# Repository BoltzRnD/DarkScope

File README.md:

(DarkScope is Still under development and might take until December 2019 for its first Functional Release.)

Darkscope is an ATSAME70Q21 Based, Open Source and Open Hardware, 4 Channel Portable DSO with Features Such as

1. 3.5" to 7" TFT
2. Internal Storage Options* (64 Mb - 256 Mb)
3. External Storage Support (MicroSD Cards and USB)
4. PC Based Expanded UI for Elaborated and Better Visualizations*.
5. Touch Screen Interface(This will be added at last.)
6. USB Type C Rev interface for Charging and Data Transfer.
7. Up to  5* MSPS (At 1 Active Channel) 
8. Up to  1* MSPS (At 4 Active Channels)

(* Chances are these will be improved by optimizing the firmware on every newer release.)

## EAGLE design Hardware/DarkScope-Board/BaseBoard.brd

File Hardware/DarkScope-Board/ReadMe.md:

# Scope

# HW Sections
1. A Baseboard that hosts All Processing (MCu and Supporting Circuitry, Expansion Ports for- Active Probe Shields, LCD, Switches) (Board 1)
2. Base Active Probe Board. i.e- Analog Channel (Board 2)
3. Battery Management Circuit(BMC) with 1500mAh or more Battery(Board 3)
4. High Speed Active Probe(Board 4)
5. Upto 4 Channel Support (Exposing/Utilizing PA0, PA4, PA5, PA6) (On BaseBoard 1)
6. (Optional) I2C Based Switch Board.(On BaseBoard 1)

Note-
1. LCD "LED-A" connected to 5V for now, can be changed to vcc

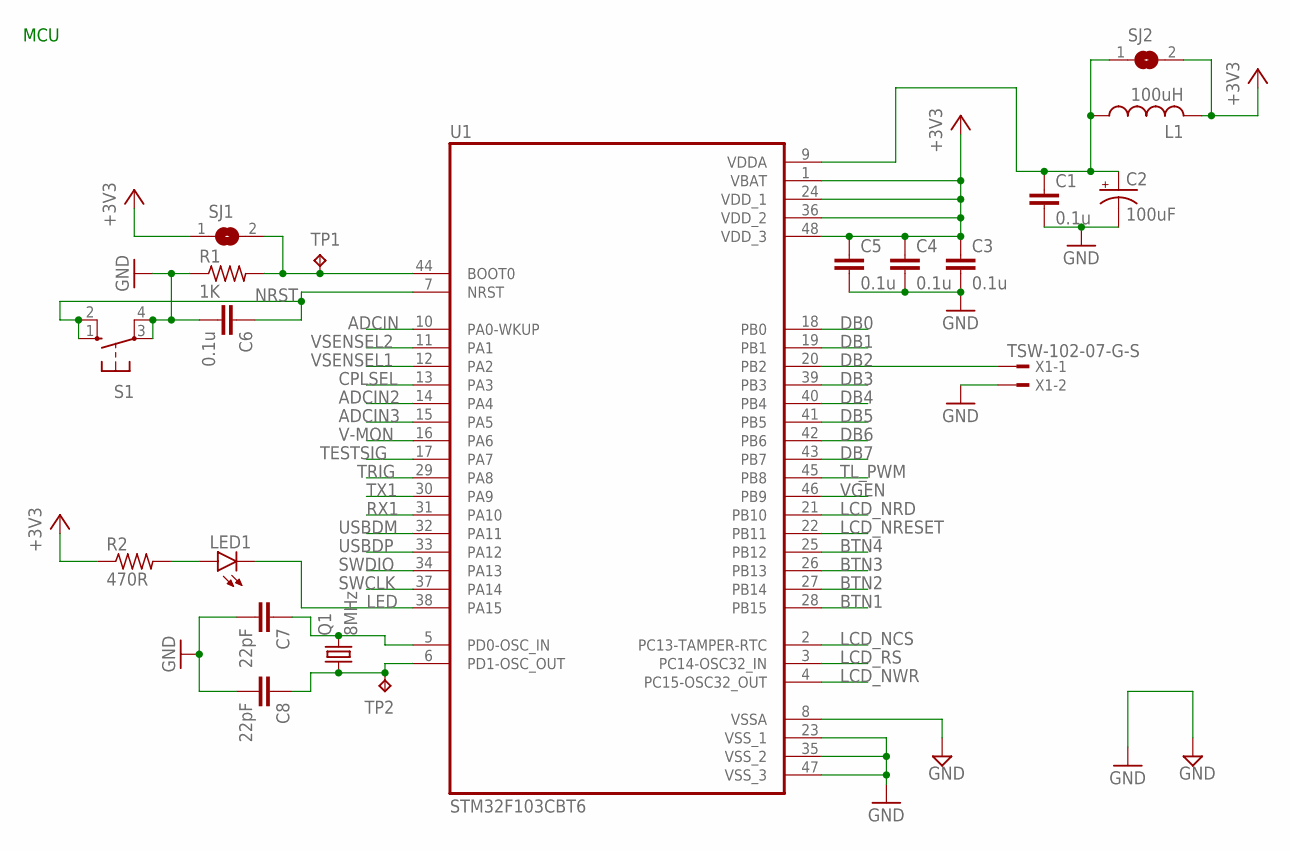
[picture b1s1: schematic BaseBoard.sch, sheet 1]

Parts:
C1, C3, C4, C5, C6: 0.1u; C1206
C2: 100uF; CT6032
C7, C8: 22pF; C1206
L1: 100uH; 0204/5
LED1: LEDCHIPLED_1206; CHIPLED_1206
Q1: 8MHz; HC49/S
R1: 1K; R0805
R2: 470R; R0805
S1: 10-XX; B3F-10XX
SJ1, SJ2: SJW
TP1, TP2: TPB1,27; B1,27
U1: STM32F103CBT6; QFP50P900X900X160-48N
X1: TSW-102-07-G-S; TSW-102-XX-G-S

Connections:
+3V3: C3.1, C4.1, C5.1, L1.2, R2.1, SJ1.1, SJ2.2, U1.1 (VBAT), U1.24 (VDD_1), U1.36 (VDD_2), U1.48 (VDD_3); also elsewhere on the board
ADCIN: U1.10 (PA0-WKUP); also elsewhere on the board
ADCIN2: U1.14 (PA4); also elsewhere on the board
ADCIN3: U1.15 (PA5); also elsewhere on the board
BTN1: U1.28 (PB15); also elsewhere on the board
BTN2: U1.27 (PB14); also elsewhere on the board
BTN3: U1.26 (PB13); also elsewhere on the board
BTN4: U1.25 (PB12); also elsewhere on the board
CPLSEL: U1.13 (PA3); also elsewhere on the board
DB0: U1.18 (PB0); also elsewhere on the board
DB1: U1.19 (PB1); also elsewhere on the board
DB2: U1.20 (PB2), X1.1; also elsewhere on the board
DB3: U1.39 (PB3); also elsewhere on the board
DB4: U1.40 (PB4); also elsewhere on the board
DB5: U1.41 (PB5); also elsewhere on the board
DB6: U1.42 (PB6); also elsewhere on the board
DB7: U1.43 (PB7); also elsewhere on the board
GND: C1.2, C2.-, C3.2, C4.2, C5.2, C6.2, C7.2, C8.2, R1.1, S1.3, S1.4 (P1), U1.8 (VSSA), U1.23 (VSS_1), U1.35 (VSS_2), U1.47 (VSS_3), X1.2; also elsewhere on the board
LCD_NCS: U1.2 (PC13-TAMPER-RTC); also elsewhere on the board
LCD_NRD: U1.21 (PB10); also elsewhere on the board
LCD_NRESET: U1.22 (PB11); also elsewhere on the board
LCD_NWR: U1.4 (PC15-OSC32_OUT); also elsewhere on the board
LCD_RS: U1.3 (PC14-OSC32_IN); also elsewhere on the board
LED: LED1.C, U1.38 (PA15); also elsewhere on the board
unnamed: C1.1, C2.+, L1.1, SJ2.1, U1.9 (VDDA)
unnamed: LED1.A, R2.2
unnamed: R1.2, SJ1.2, TP1.TP, U1.44 (BOOT0)
unnamed: C7.1, Q1.2, U1.5 (PD0-OSC_IN)
unnamed: C8.1, Q1.1, TP2.TP, U1.6 (PD1-OSC_OUT)
NRST: C6.1, S1.1 (S), S1.2 (S1), U1.7 (NRST); also elsewhere on the board
RX1: U1.31 (PA10); also elsewhere on the board
SWCLK: U1.37 (PA14); also elsewhere on the board
SWDIO: U1.34 (PA13); also elsewhere on the board
TESTSIG: U1.17 (PA7); also elsewhere on the board
TL_PWM: U1.45 (PB8); also elsewhere on the board
TRIG: U1.29 (PA8); also elsewhere on the board
TX1: U1.30 (PA9); also elsewhere on the board
USBDM: U1.32 (PA11); also elsewhere on the board
USBDP: U1.33 (PA12); also elsewhere on the board
V-MON: U1.16 (PA6); also elsewhere on the board
VGEN: U1.46 (PB9); also elsewhere on the board
VSENSEL1: U1.12 (PA2); also elsewhere on the board
VSENSEL2: U1.11 (PA1); also elsewhere on the board

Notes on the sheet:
MCU

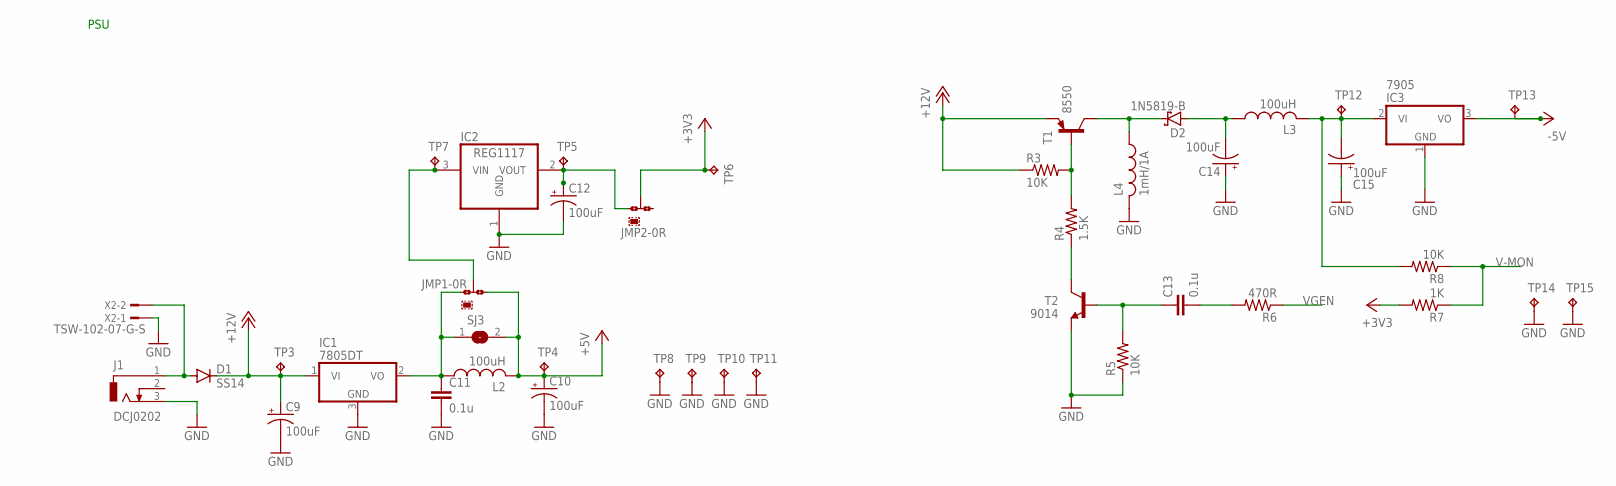
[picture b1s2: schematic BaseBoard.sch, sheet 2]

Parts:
C9, C10, C12, C14, C15: 100uF; CT6032
C11, C13: 0.1u; C1206
D1: SS14; SMB
D2: 1N5819-B; DO41-7.6
IC1: 7805DT; TO252
IC2: REG1117; SOT223
IC3: 7905; TO92
J1: DCJ0202
JMP1, JMP2: 0R-JUMPA; A0R-JMP
L2, L3: 100uH; 0204/5
L4: 1mH/1A; 6000-XXXX-RC
R3, R5, R8: 10K; R0805
R4: 1.5K; R0805
R6: 470R; R0805
R7: 1K; R0805
SJ3: SJW
T1: 8550; TO92
T2: 9014; TO92
TP3, TP4, TP5, TP6, TP7, TP8, TP9, TP10, TP11, TP12, TP13, TP14, TP15: TPB1,27; B1,27
X2: TSW-102-07-G-S; TSW-102-XX-G-S

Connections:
+3V3: JMP2.2, R7.2, TP6.TP; also elsewhere on the board
+5V: C10.+, JMP1.3, L2.2, SJ3.2, TP4.TP; also elsewhere on the board
+12V: C9.+, D1.C, IC1.1 (VI), R3.1, T1.1 (E), TP3.TP; also elsewhere on the board
-5V: IC3.3 (VO), TP13.TP; also elsewhere on the board
GND: C9.-, C10.-, C11.2, C12.-, C14.+, C15.+, IC1.3 (GND), IC2.1 (GND), IC3.1 (GND), J1.3, L4.2, R5.1, T2.1 (E), TP8.TP, TP9.TP, TP10.TP, TP11.TP, TP14.TP, TP15.TP, X2.1; also elsewhere on the board
unnamed: C11.1, IC1.2 (VO), JMP1.1, L2.1, SJ3.1
unnamed: R3.2, R4.2, T1.2 (B)
unnamed: C12.+, IC2.2 (VOUT), JMP2.1, TP5.TP
unnamed: R4.1, T2.3 (C)
unnamed: C13.1, R5.2, T2.2 (B)
unnamed: IC2.3 (VIN), JMP1.2, TP7.TP
unnamed: C13.2, R6.2
unnamed: D2.C, L4.1, T1.3 (C)
unnamed: C14.-, D2.A, L3.1
unnamed: C15.-, IC3.2 (VI), L3.2, R8.2, TP12.TP
unnamed: D1.A, J1.1, X2.2
V-MON: R7.1, R8.1; also elsewhere on the board
VGEN: R6.1; also elsewhere on the board

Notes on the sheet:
PSU

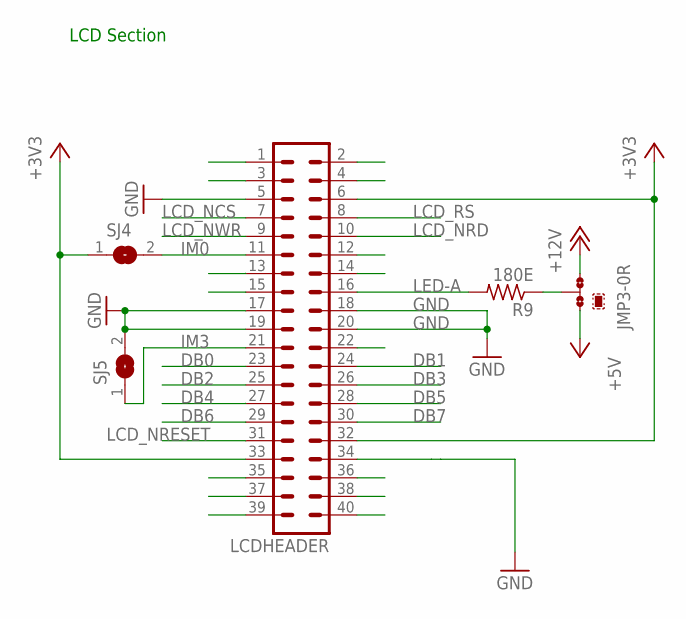
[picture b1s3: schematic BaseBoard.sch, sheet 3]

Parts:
JMP3: 0R-JUMPA; A0R-JMP
LCDHEADER: MA20-2
R9: 180E; R0805
SJ4, SJ5: SJ

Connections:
+3V3: LCDHEADER.6, LCDHEADER.32, LCDHEADER.33, SJ4.1; also elsewhere on the board
+5V: JMP3.1; also elsewhere on the board
+12V: JMP3.3; also elsewhere on the board
DB0: LCDHEADER.23; also elsewhere on the board
DB1: LCDHEADER.24; also elsewhere on the board
DB2: LCDHEADER.25; also elsewhere on the board
DB3: LCDHEADER.26; also elsewhere on the board
DB4: LCDHEADER.27; also elsewhere on the board
DB5: LCDHEADER.28; also elsewhere on the board
DB6: LCDHEADER.29; also elsewhere on the board
DB7: LCDHEADER.30; also elsewhere on the board
GND: LCDHEADER.5, LCDHEADER.17, LCDHEADER.18, LCDHEADER.19, LCDHEADER.20, LCDHEADER.34, SJ5.2; also elsewhere on the board
IM0: LCDHEADER.11, SJ4.2
IM3: LCDHEADER.21, SJ5.1
LCD_NCS: LCDHEADER.7; also elsewhere on the board
LCD_NRD: LCDHEADER.10; also elsewhere on the board
LCD_NRESET: LCDHEADER.31; also elsewhere on the board
LCD_NWR: LCDHEADER.9; also elsewhere on the board
LCD_RS: LCDHEADER.8; also elsewhere on the board
LED-A: LCDHEADER.16, R9.2
LED-K1: LCDHEADER.15
unnamed: JMP3.2, R9.1

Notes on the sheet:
LCD Section

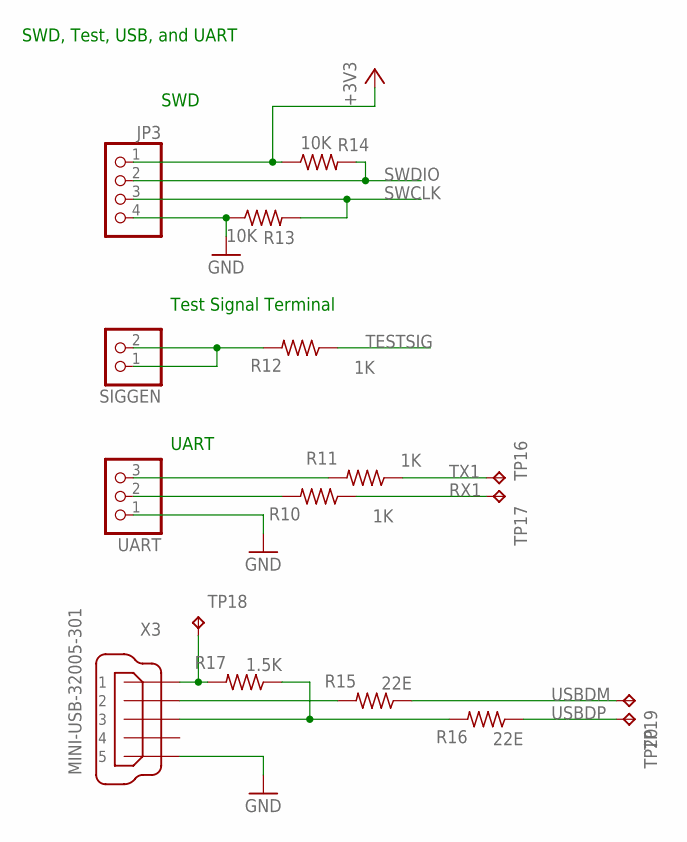
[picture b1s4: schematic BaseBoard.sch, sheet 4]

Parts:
JP3: PINHD-1X4; 1X04
R10, R11, R12: 1K; R0805
R13, R14: 10K; R0805
R15, R16: 22E; R0805
R17: 1.5K; R0805
SIGGEN: PINHD-1X2; 1X02
TP16, TP17, TP18, TP19, TP20: TPB1,27; B1,27
UART: PINHD-1X3; 1X03
X3: MINI-USB-32005-301; 32005-301

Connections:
+3V3: JP3.1, R14.1; also elsewhere on the board
GND: JP3.4, R13.1, UART.1, X3.5; also elsewhere on the board
unnamed: R10.2, UART.2
unnamed: R11.2, UART.3
unnamed: R12.2, SIGGEN.1, SIGGEN.2
unnamed: R17.2, TP18.TP, X3.1
unnamed: R16.2, R17.1, X3.3
unnamed: R15.2, X3.2
RX1: R10.1, TP17.TP; also elsewhere on the board
SWCLK: JP3.3, R13.2; also elsewhere on the board
SWDIO: JP3.2, R14.2; also elsewhere on the board
TESTSIG: R12.1; also elsewhere on the board
TX1: R11.1, TP16.TP; also elsewhere on the board
USBDM: R15.1, TP19.TP; also elsewhere on the board
USBDP: R16.1, TP20.TP; also elsewhere on the board

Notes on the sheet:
SWD, Test, USB, and UART
UART
Test Signal Terminal
SWD

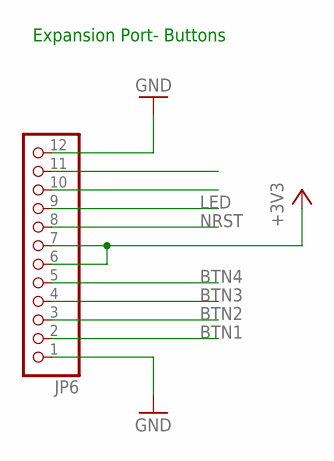
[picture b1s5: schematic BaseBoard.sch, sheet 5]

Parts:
JP6: PINHD-1X12; 1X12

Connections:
+3V3: JP6.6, JP6.7; also elsewhere on the board
BTN1: JP6.2; also elsewhere on the board
BTN2: JP6.3; also elsewhere on the board
BTN3: JP6.4; also elsewhere on the board
BTN4: JP6.5; also elsewhere on the board
GND: JP6.1, JP6.12; also elsewhere on the board
LED: JP6.9; also elsewhere on the board
NRST: JP6.8; also elsewhere on the board

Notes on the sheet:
Expansion Port- Buttons

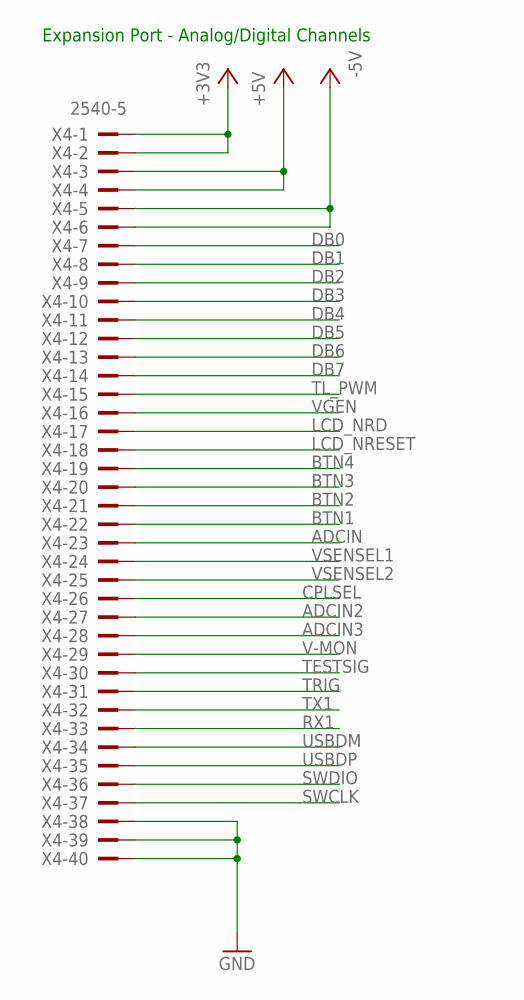
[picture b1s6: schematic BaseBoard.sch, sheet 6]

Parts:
X4: 2540-5; PAK100/2500-5-40

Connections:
+3V3: X4.1, X4.2; also elsewhere on the board
+5V: X4.3, X4.4; also elsewhere on the board
-5V: X4.5, X4.6; also elsewhere on the board
ADCIN: X4.23; also elsewhere on the board
ADCIN2: X4.27; also elsewhere on the board
ADCIN3: X4.28; also elsewhere on the board
BTN1: X4.22; also elsewhere on the board
BTN2: X4.21; also elsewhere on the board
BTN3: X4.20; also elsewhere on the board
BTN4: X4.19; also elsewhere on the board
CPLSEL: X4.26; also elsewhere on the board
DB0: X4.7; also elsewhere on the board
DB1: X4.8; also elsewhere on the board
DB2: X4.9; also elsewhere on the board
DB3: X4.10; also elsewhere on the board
DB4: X4.11; also elsewhere on the board
DB5: X4.12; also elsewhere on the board
DB6: X4.13; also elsewhere on the board
DB7: X4.14; also elsewhere on the board
GND: X4.38, X4.39, X4.40; also elsewhere on the board
LCD_NRD: X4.17; also elsewhere on the board
LCD_NRESET: X4.18; also elsewhere on the board
RX1: X4.33; also elsewhere on the board
SWCLK: X4.37; also elsewhere on the board
SWDIO: X4.36; also elsewhere on the board
TESTSIG: X4.30; also elsewhere on the board
TL_PWM: X4.15; also elsewhere on the board
TRIG: X4.31; also elsewhere on the board
TX1: X4.32; also elsewhere on the board
USBDM: X4.34; also elsewhere on the board
USBDP: X4.35; also elsewhere on the board
V-MON: X4.29; also elsewhere on the board
VGEN: X4.16; also elsewhere on the board
VSENSEL1: X4.24; also elsewhere on the board
VSENSEL2: X4.25; also elsewhere on the board

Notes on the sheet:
Expansion Port - Analog/Digital Channels

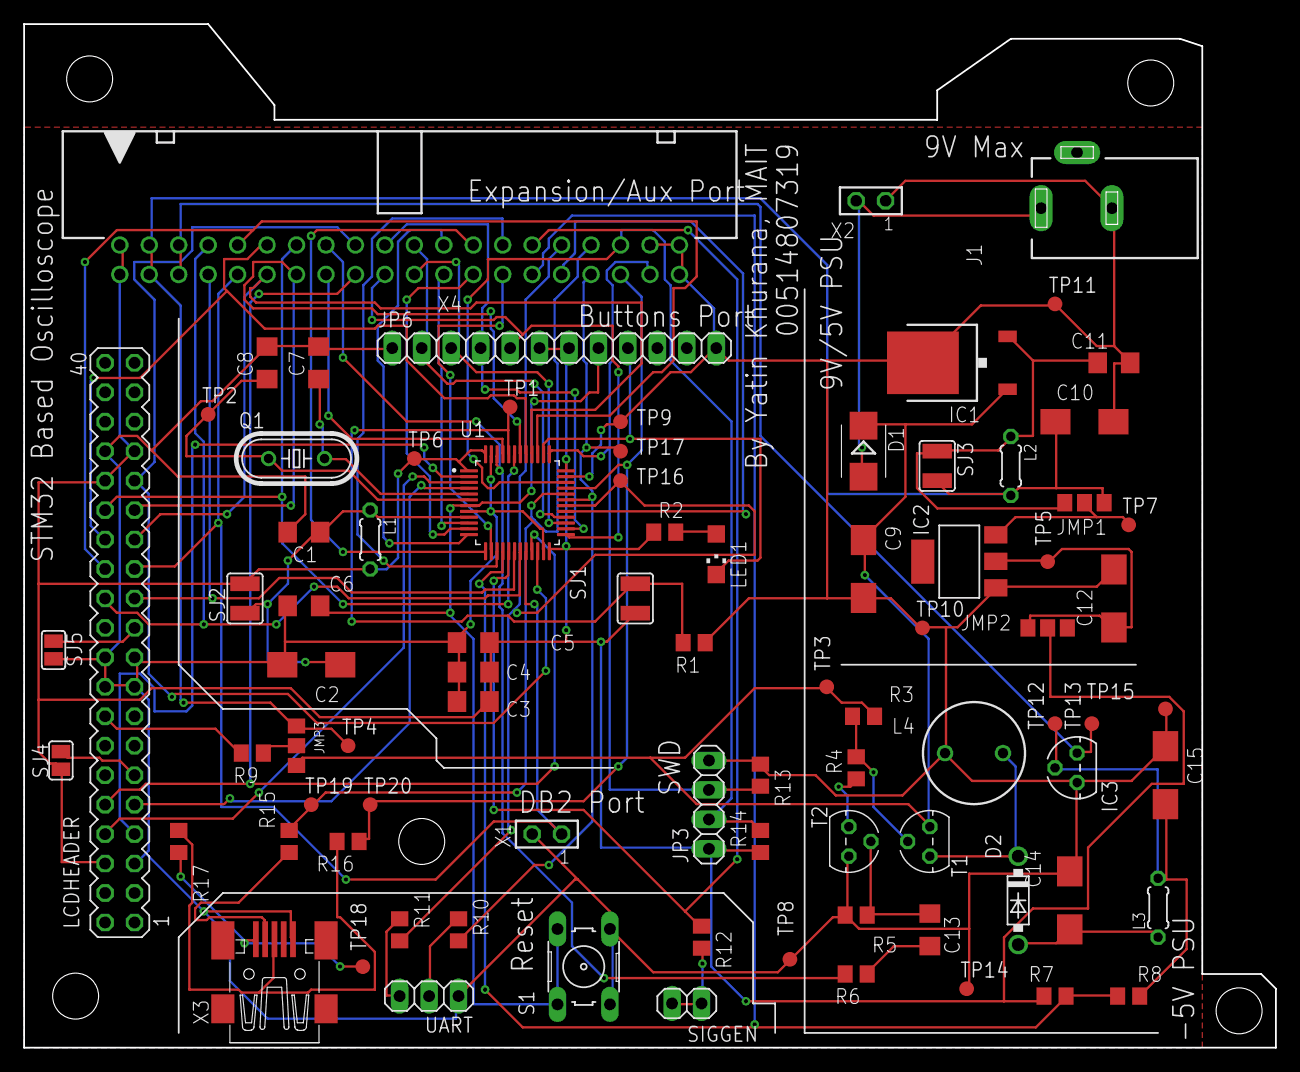
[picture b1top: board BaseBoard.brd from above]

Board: 2 copper layers, 108.0 x 88.3 mm, 90 parts (0 on the bottom side), 67 nets.

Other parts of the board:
U$1, U$2, U$3, U$4, U$5: DRILL_0.1560

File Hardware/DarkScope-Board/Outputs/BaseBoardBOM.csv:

Part,Value,Device,Package,Description,AVAILABILITY,DESCRIPTION,MF,MP,MPN,OC_FARNELL,OC_NEWARK,PACKAGE,POPULARITY,PRICE,PURCHASE-URL,SPICEPREFIX,TP_SIGNAL_NAME
C1,0.1u,C-EUC1206,C1206,"CAPACITOR, European symbol",,,,,,,,,54,,,C,
C2,100uF,CPOL-USCT6032,CT6032,"POLARIZED CAPACITOR, American symbol",,,,,,,,,0,,,C,
C3,0.1u,C-EUC1206,C1206,"CAPACITOR, European symbol",,,,,,,,,54,,,C,
C4,0.1u,C-EUC1206,C1206,"CAPACITOR, European symbol",,,,,,,,,54,,,C,
C5,0.1u,C-EUC1206,C1206,"CAPACITOR, European symbol",,,,,,,,,54,,,C,
C6,0.1u,C-EUC1206,C1206,"CAPACITOR, European symbol",,,,,,,,,54,,,C,
C7,22pF,C-EUC1206,C1206,"CAPACITOR, European symbol",,,,,,,,,54,,,C,
C8,22pF,C-EUC1206,C1206,"CAPACITOR, European symbol",,,,,,,,,54,,,C,
C9,100uF,CPOL-USCT6032,CT6032,"POLARIZED CAPACITOR, American symbol",,,,,,,,,0,,,C,
C10,100uF,CPOL-USCT6032,CT6032,"POLARIZED CAPACITOR, American symbol",,,,,,,,,0,,,C,
C11,0.1u,C-EUC1206,C1206,"CAPACITOR, European symbol",,,,,,,,,54,,,C,
C12,100uF,CPOL-USCT6032,CT6032,"POLARIZED CAPACITOR, American symbol",,,,,,,,,0,,,C,
C13,0.1u,C-EUC1206,C1206,"CAPACITOR, European symbol",,,,,,,,,54,,,C,
C14,100uF,CPOL-USCT6032,CT6032,"POLARIZED CAPACITOR, American symbol",,,,,,,,,0,,,C,
C15,100uF,CPOL-USCT6032,CT6032,"POLARIZED CAPACITOR, American symbol",,,,,,,,,0,,,C,
D1,SS14,ES2D,SMB,DIODE,,,,,,,,,3,,,,
D2,1N5819-B,1N5819-B,DO41-7.6,1.0A SCHOTTKY BARRIER RECTIFIER,,,,,,,,,11,,,,
IC1,7805DT,7805DT,TO252,Positive VOLTAGE REGULATOR,,,,,,,,,0,,,,
IC2,REG1117,REG1117,SOT223,800mA and 1A Low Dropout (LDO) Positive Regulator,,,,,REG1117,1097566,14P6981,,49,,,,
IC3,7905,79L05Z,TO92,Negative VOLTAGE REGULATOR,,,,,,,,,0,,,,
J1,DCJ0202,DCJ0202,DCJ0202,DC POWER JACK,,,,,,unknown,unknown,,17,,,,
JMP1,0R-JUMPC,0R-JUMPC,C0R-JMP,SMD 0R 0805 Jumper,,,,,,,,,0,,,,
JMP2,0R-JUMPC,0R-JUMPC,C0R-JMP,SMD 0R 0805 Jumper,,,,,,,,,0,,,,
JMP3,0R-JUMPC,0R-JUMPC,C0R-JMP,SMD 0R 0805 Jumper,,,,,,,,,0,,,,
JP3,,PINHD-1X4,1X04,PIN HEADER,,,,,,,,,91,,,,
JP6,,PINHD-1X12,1X12,PIN HEADER,,,,,,,,,28,,,,
L1,100uH,L-US0204/5,0204/5,"INDUCTOR, American symbol",,,,,,,,,0,,,L,
L2,100uH,L-US0204/5,0204/5,"INDUCTOR, American symbol",,,,,,,,,0,,,L,
L3,100uH,L-US0204/5,0204/5,"INDUCTOR, American symbol",,,,,,,,,0,,,L,
L4,1mH/1A,L-US6000-XXX-RC,6000-XXXX-RC,"INDUCTOR, American symbol",,,,,,,,,5,,,L,
LCDHEADER,,MA20-2,MA20-2,PIN HEADER,,,,,,unknown,unknown,,1,,,,
LED1,,LEDCHIPLED_1206,CHIPLED_1206,LED,,,,,,,,,28,,,,
Q1,8MHz,CRYSTALHC49S,HC49/S,CRYSTAL,,,,,,1667008,unknown,,49,,,,
R1,1K,R-US_R0805,R0805,"RESISTOR, American symbol",,,,,,,,,85,,,R,
R2,470R,R-US_R0805,R0805,"RESISTOR, American symbol",,,,,,,,,85,,,R,
R3,10K,R-US_R0805,R0805,"RESISTOR, American symbol",,,,,,,,,85,,,R,
R4,1.5K,R-US_R0805,R0805,"RESISTOR, American symbol",,,,,,,,,85,,,R,
R5,10K,R-US_R0805,R0805,"RESISTOR, American symbol",,,,,,,,,85,,,R,
R6,470R,R-US_R0805,R0805,"RESISTOR, American symbol",,,,,,,,,85,,,R,
R7,1K,R-US_R0805,R0805,"RESISTOR, American symbol",,,,,,,,,85,,,R,
R8,10K,R-US_R0805,R0805,"RESISTOR, American symbol",,,,,,,,,85,,,R,
R9,180E,R-US_R0805,R0805,"RESISTOR, American symbol",,,,,,,,,85,,,R,
R10,1K,R-US_R0805,R0805,"RESISTOR, American symbol",,,,,,,,,85,,,R,
R11,1K,R-US_R0805,R0805,"RESISTOR, American symbol",,,,,,,,,85,,,R,
R12,1K,R-US_R0805,R0805,"RESISTOR, American symbol",,,,,,,,,85,,,R,
R13,10K,R-US_R0805,R0805,"RESISTOR, American symbol",,,,,,,,,85,,,R,
R14,10K,R-US_R0805,R0805,"RESISTOR, American symbol",,,,,,,,,85,,,R,
R15,22E,R-US_R0805,R0805,"RESISTOR, American symbol",,,,,,,,,85,,,R,
R16,22E,R-US_R0805,R0805,"RESISTOR, American symbol",,,,,,,,,85,,,R,
R17,1.5K,R-US_R0805,R0805,"RESISTOR, American symbol",,,,,,,,,85,,,R,
S1,,10-XX,B3F-10XX,OMRON SWITCH,,,,,B3F-1000,176432,36M3542,,72,,,,
SIGGEN,,PINHD-1X2,1X02,PIN HEADER,,,,,,,,,98,,,,
SJ1,,SJW,SJW,SMD solder JUMPER,,,,,,,,,3,,,,
SJ2,,SJW,SJW,SMD solder JUMPER,,,,,,,,,3,,,,
SJ3,,SJW,SJW,SMD solder JUMPER,,,,,,,,,3,,,,
SJ4,,SJ,SJ,SMD solder JUMPER,,,,,,,,,33,,,,
SJ5,,SJ,SJ,SMD solder JUMPER,,,,,,,,,33,,,,
T1,8550,#NAME?,TO92,PNP Transistror,,,,,,,,,0,,,,
T2,9014,#NAME?,TO92,NPN Transistror,,,,,,,,,0,,,,
TP1,"TPB1,27","TPB1,27","B1,27",Test pad,,,,,,,,,19,,,,
TP2,"TPB1,27","TPB1,27","B1,27",Test pad,,,,,,,,,19,,,,
TP3,"TPB1,27","TPB1,27","B1,27",Test pad,,,,,,,,,19,,,,
TP4,"TPB1,27","TPB1,27","B1,27",Test pad,,,,,,,,,19,,,,
TP5,"TPB1,27","TPB1,27","B1,27",Test pad,,,,,,,,,19,,,,
TP6,"TPB1,27","TPB1,27","B1,27",Test pad,,,,,,,,,19,,,,
TP7,"TPB1,27","TPB1,27","B1,27",Test pad,,,,,,,,,19,,,,
TP8,"TPB1,27","TPB1,27","B1,27",Test pad,,,,,,,,,19,,,,
TP9,"TPB1,27","TPB1,27","B1,27",Test pad,,,,,,,,,19,,,,
TP10,"TPB1,27","TPB1,27","B1,27",Test pad,,,,,,,,,19,,,,
TP11,"TPB1,27","TPB1,27","B1,27",Test pad,,,,,,,,,19,,,,
TP12,"TPB1,27","TPB1,27","B1,27",Test pad,,,,,,,,,19,,,,
TP13,"TPB1,27","TPB1,27","B1,27",Test pad,,,,,,,,,19,,,,
TP14,"TPB1,27","TPB1,27","B1,27",Test pad,,,,,,,,,19,,,,
TP15,"TPB1,27","TPB1,27","B1,27",Test pad,,,,,,,,,19,,,,
TP16,"TPB1,27","TPB1,27","B1,27",Test pad,,,,,,,,,19,,,,
TP17,"TPB1,27","TPB1,27","B1,27",Test pad,,,,,,,,,19,,,,
TP18,"TPB1,27","TPB1,27","B1,27",Test pad,,,,,,,,,19,,,,
TP19,"TPB1,27","TPB1,27","B1,27",Test pad,,,,,,,,,19,,,,
TP20,"TPB1,27","TPB1,27","B1,27",Test pad,,,,,,,,,19,,,,
U1,STM32F103CBT6,STM32F103CBT6,QFP50P900X900X160-48N,"Mainstream Performance line, ARM Cortex-M3 MCU with 128 Kbytes Flash, 72 MHz CPU, motor control, USB and CAN Check prices",In Stock, ARM® Cortex®-M3 STM32F1 Microcontroller IC 32-Bit 72MHz 128KB (128K x 8) FLASH ,STMicroelectronics,STM32F103CBT6,,,,LQFP-48 STMicroelectronics,,None,https://pricing.snapeda.com/search/part/STM32F103CBT6/?ref=eda,,
UART,,PINHD-1X3,1X03,PIN HEADER,,,,,,,,,92,,,,
X1,TSW-102-07-G-S,TSW-102-07-G-S,TSW-102-XX-G-S,"THROUGH-HOLE .025 SQ POST HEADER""",,,Samtec Inc.,,TSW-102-07-G-S,,,,,,,,
X2,TSW-102-07-G-S,TSW-102-07-G-S,TSW-102-XX-G-S,"THROUGH-HOLE .025 SQ POST HEADER""",,,Samtec Inc.,,TSW-102-07-G-S,,,,,,,,
X3,MINI-USB-32005-301,MINI-USB-32005-301,32005-301,MINI USB-B Conector,,,,,,unknown,unknown,,0,,,,
X4,2540-5,2540-5,PAK100/2500-5-40,3M (TM) Pak 100 4-Wall Header,,,,,,9838414,unknown,,0,,,,

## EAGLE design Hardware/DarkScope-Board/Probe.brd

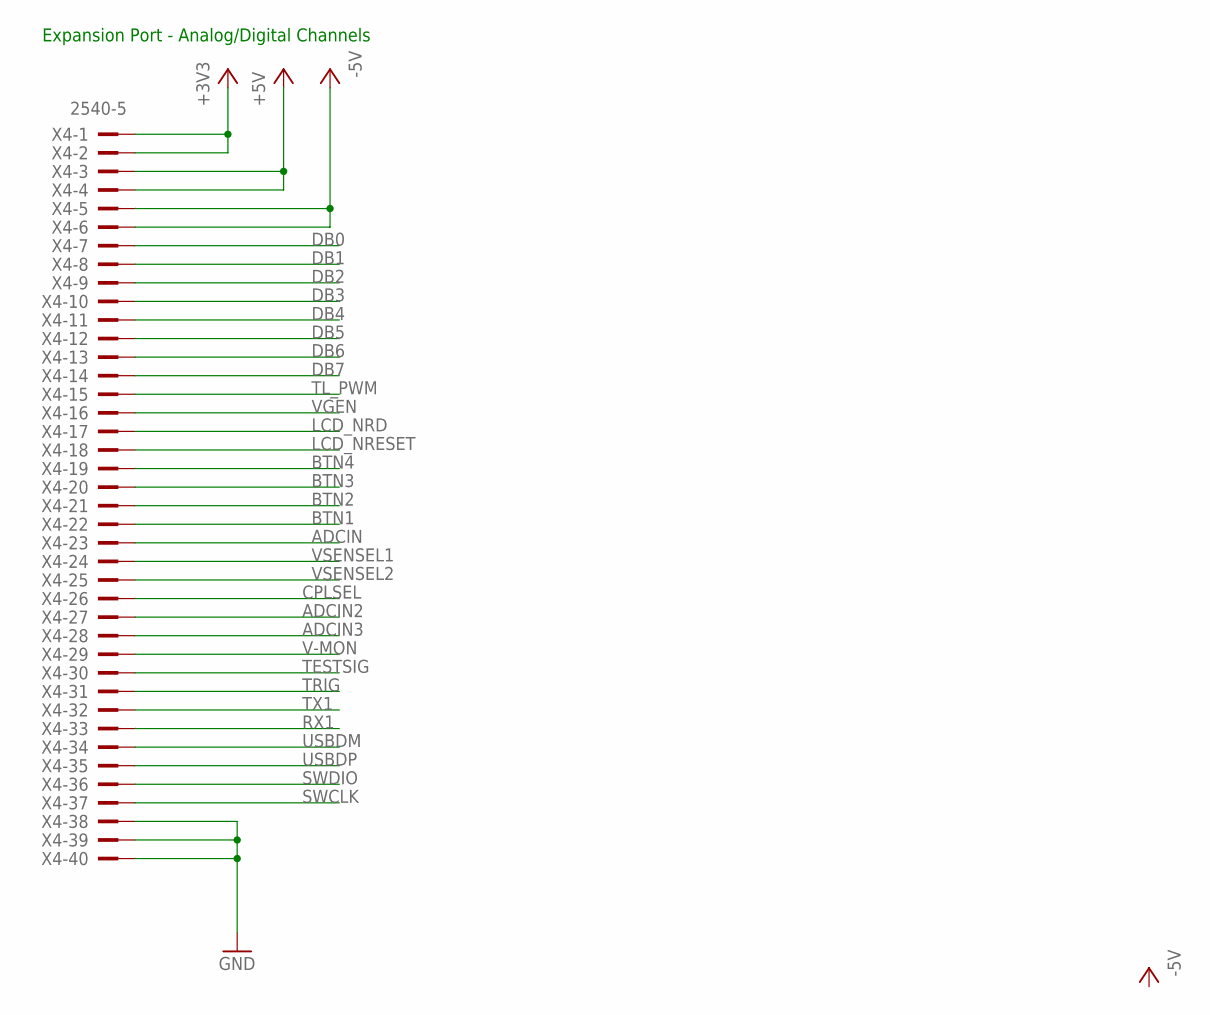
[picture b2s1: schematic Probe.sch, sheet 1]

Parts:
X4: 2540-5; PAK100/2500-5-40

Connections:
+3V3: X4.1, X4.2
+5V: X4.3, X4.4; also elsewhere on the board
-5V: X4.5, X4.6; also elsewhere on the board
ADCIN: X4.23; also elsewhere on the board
ADCIN2: X4.27
ADCIN3: X4.28
BTN1: X4.22
BTN2: X4.21
BTN3: X4.20
BTN4: X4.19
CPLSEL: X4.26; also elsewhere on the board
DB0: X4.7
DB1: X4.8
DB2: X4.9
DB3: X4.10
DB4: X4.11
DB5: X4.12
DB6: X4.13
DB7: X4.14
GND: X4.38, X4.39, X4.40; also elsewhere on the board
LCD_NRD: X4.17
LCD_NRESET: X4.18
RX1: X4.33
SWCLK: X4.37
SWDIO: X4.36
TESTSIG: X4.30
TL_PWM: X4.15; also elsewhere on the board
TRIG: X4.31; also elsewhere on the board
TX1: X4.32
USBDM: X4.34
USBDP: X4.35
V-MON: X4.29
VGEN: X4.16
VSENSEL1: X4.24; also elsewhere on the board
VSENSEL2: X4.25; also elsewhere on the board

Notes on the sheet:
Expansion Port - Analog/Digital Channels

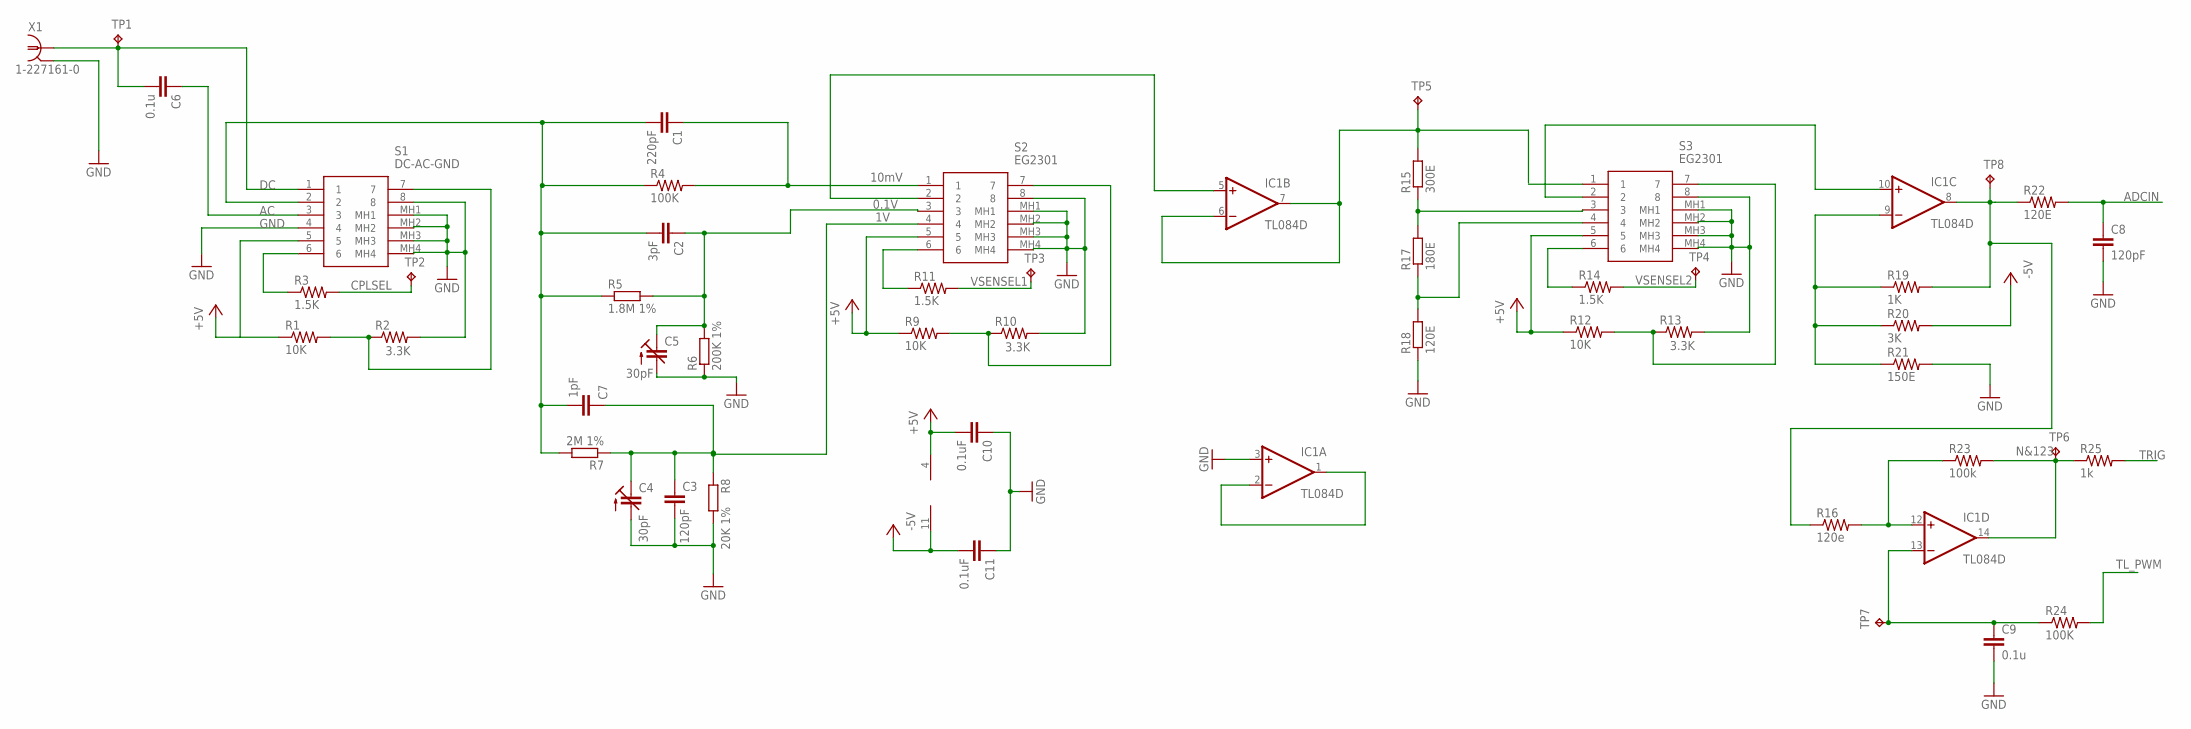
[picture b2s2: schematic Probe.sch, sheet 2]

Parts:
C1: 220pF; C1206
C2: 3pF; C1206
C3, C8: 120pF; C2.5-3
C4, C5: 30pF; CTRIM808-BC
C6: 0.1u; C1206
C7: 1pF; C1206
C9: 0.1u; C2.5-3
C10, C11: 0.1uF; C1206
IC1: TL084D; SO14
R1, R9, R12: 10K; R0805
R2, R10, R13: 3.3K; R0805
R3, R11, R14: 1.5K; R0805
R4, R24: 100K; R0805
R5: 1.8M 1%; 0204/7
R6: 200K 1%; 0204/7
R7: 2M 1%; 0204/7
R8: 20K 1%; 0204/7
R15: 300E; 0204/7
R16: 120e; R0805
R17: 180E; 0204/7
R18: 120E; 0204/7
R19: 1K; R0805
R20: 3K; R0805
R21: 150E; R0805
R22: 120E; R0805
R23: 100k; R0805
R25: 1k; R0805
S1: DC-AC-GND; EG2301
S2, S3: EG2301
TP1, TP2, TP3, TP4, TP5, TP6, TP7, TP8: TPB1,27; B1,27
X1: 1-227161-0; AMP_227161

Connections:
+5V: C10.2, IC1.4 (V+), R1.1, R9.1, R12.1, S1.5, S2.5, S3.5; also elsewhere on the board
-5V: C11.2, IC1.11 (V-), R20.2; also elsewhere on the board
ADCIN: C8.1, R22.2; also elsewhere on the board
CPLSEL: R3.2, TP2.TP; also elsewhere on the board
GND: C3.2, C4.2 (A), C5.2 (A), C8.2, C9.2, C10.1, C11.1, IC1.3 (+IN), R2.2, R6.1, R8.2, R10.2, R13.2, R18.1, R21.2, S1.4, S1.8, S1.MH1, S1.MH2, S1.MH3, S1.MH4, S2.8, S2.MH1, S2.MH2, S2.MH3, S2.MH4, S3.8, S3.MH1, S3.MH2, S3.MH3, S3.MH4, X1.2; also elsewhere on the board
unnamed: C6.2, S1.1, TP1.TP, X1.1
unnamed: C6.1, S1.3
unnamed: R3.1, S1.6
unnamed: R1.2, R2.1, S1.7
unnamed: C1.2, C2.2, C7.2, R4.1, R5.1, R7.2, S1.2
unnamed: C3.1, C4.1 (E), C7.1, R7.1, R8.1, S2.4
unnamed: C1.1, R4.2, S2.1
unnamed: C2.1, C5.1 (E), R5.2, R6.2, S2.3
unnamed: IC1.5 (+IN), S2.2
unnamed: R15.1, R17.2, S3.3
unnamed: R9.2, R10.1, S2.7
unnamed: R11.1, S2.6
unnamed: R12.2, R13.1, S3.7
unnamed: R14.1, S3.6
unnamed: IC1.10 (+IN), S3.2
unnamed: R17.1, R18.2, S3.4
unnamed: IC1.9 (-IN), R19.1, R20.1, R21.1
unnamed: IC1.1 (OUT), IC1.2 (-IN)
unnamed: IC1.12 (+IN), R16.2, R23.1
unnamed: IC1.8 (OUT), R16.1, R19.2, R22.1, TP8.TP
unnamed: C9.1, IC1.13 (-IN), R24.1, TP7.TP
N&123: IC1.14 (OUT), R23.2, R25.1, TP6.TP
TL_PWM: R24.2; also elsewhere on the board
TRIG: R25.2; also elsewhere on the board
VSENSEL1: R11.2, TP3.TP; also elsewhere on the board
VSENSEL2: R14.2, TP4.TP; also elsewhere on the board

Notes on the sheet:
GND
10mV
0.1V

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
